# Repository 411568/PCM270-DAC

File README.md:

<h2>🧐 Features</h2>

USB DAC based on the PCM270xC iC. Powered by a USB type C connector. Output is compliant with the Line Out specification.
The included gerber files and BOM are made for JLCPCB. All of the components are taken from the LCSC library, meaning you can have the board assembled by JLC.
Important note: the board has not been tested yet.

<h2>🛡️ License:</h2>

This project is licensed under the MIT License.

<h2> 🙋‍♂️Authors </h2>

- Krzysztof Sikora

<h2>💖Like my work?</h2>

If you have any questions about the project feel free to contact us via email: krzysieksikora717@gmail.com

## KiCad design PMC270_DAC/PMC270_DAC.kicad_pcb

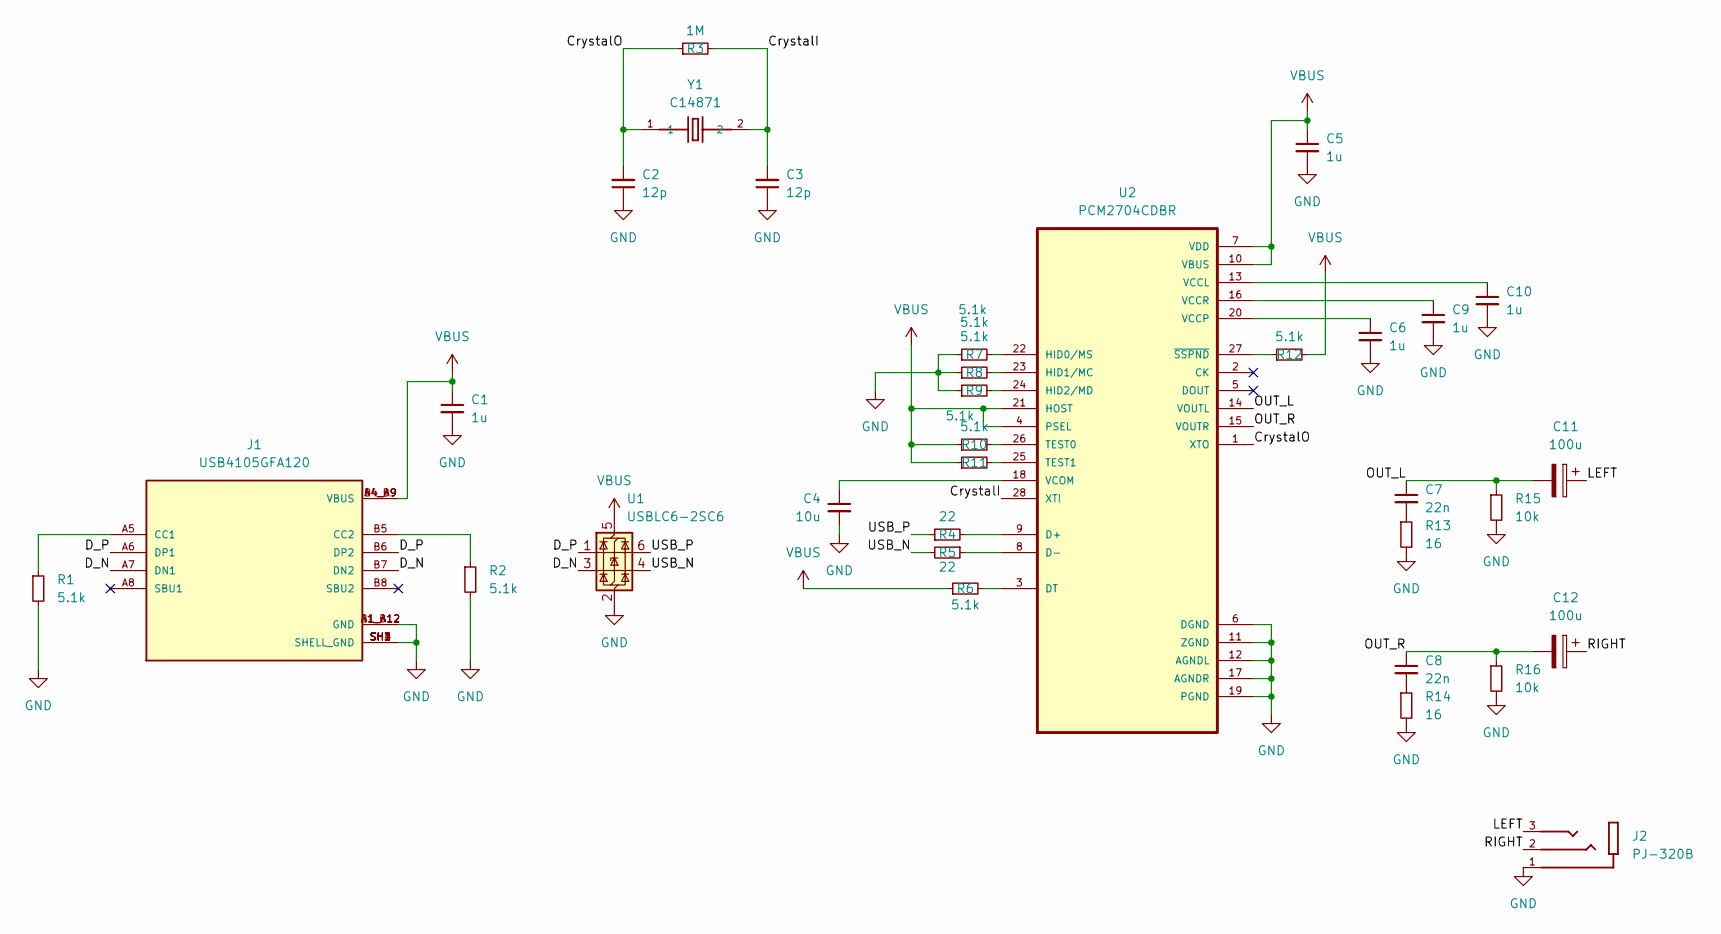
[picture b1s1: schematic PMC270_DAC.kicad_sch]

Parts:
C1, C5, C6, C9, C10: 1u; C_0805_2012Metric_Pad1.18x1.45mm_HandSolder
C2, C3: 12p; C_0603_1608Metric_Pad1.08x0.95mm_HandSolder
C4: 10u; C_0805_2012Metric_Pad1.18x1.45mm_HandSolder
C7, C8: 22n; C_0603_1608Metric_Pad1.08x0.95mm_HandSolder
C11, C12: 100u; C_Elec_6.3x7.7
J1: USB4105GFA120; GCT_USB4105GFA120; PARTREV B3
J2: PJ-320B; BOOMELE_PJ-320B
R1, R2, R6, R7, R8, R9, R10, R11, R12: 5.1k; R_0603_1608Metric_Pad0.98x0.95mm_HandSolder
R3: 1M; R_0603_1608Metric_Pad0.98x0.95mm_HandSolder
R4, R5: 22; R_0603_1608Metric_Pad0.98x0.95mm_HandSolder
R13, R14: 16; R_0603_1608Metric_Pad0.98x0.95mm_HandSolder
R15, R16: 10k; R_0603_1608Metric_Pad0.98x0.95mm_HandSolder
U1: USBLC6-2SC6; SOT-23-6
U2: PCM2704CDBR; SOP65P780X200-28N
Y1: C14871; XTAL1170X500X450

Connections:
/CrystalI: C3.2, R3.2, U2.28 (XTI), Y1.2
/CrystalO: C2.2, R3.1, U2.1 (XTO), Y1.1
/D_N: J1.A7 (DN1), J1.B7 (DN2), U1.3 (I/O2); also elsewhere on the board
/D_P: J1.A6 (DP1), J1.B6 (DP2), U1.1 (I/O1); also elsewhere on the board
/LEFT: C11.1, J2.3; also elsewhere on the board
/OUT_L: C7.1, C11.2, R15.1, U2.14 (VOUTL)
/OUT_R: C8.1, C12.2, R16.1, U2.15 (VOUTR)
/RIGHT: C12.1, J2.2; also elsewhere on the board
/USB_N: R5.2, U1.4 (I/O2)
/USB_P: R4.1, U1.6 (I/O1)
GND: C1.2, C2.1, C3.1, C4.2, C5.2, C6.2, C9.2, C10.2, J1.A1_B12 (GND), J1.B1_A12 (GND), J1.SH1 (SHELL_GND), J1.SH2 (SHELL_GND), J1.SH3 (SHELL_GND), J1.SH4 (SHELL_GND), J2.1, R1.2, R2.2, R7.1, R8.1, R9.1, R13.2, R14.2, R15.2, R16.2, U1.2 (GND), U2.6 (DGND), U2.11 (ZGND), U2.12 (AGNDL), U2.17 (AGNDR), U2.19 (PGND); also elsewhere on the board
unnamed: C7.2, R13.1
unnamed: C8.2, R14.1
unnamed 13: J1.A5 (CC1), R1.1; also elsewhere on the board
unnamed 14: J1.B5 (CC2), R2.1; also elsewhere on the board
unnamed: R4.2, U2.9 (D+)
unnamed: R5.1, U2.8 (D-)
unnamed: R6.2, U2.3 (DT)
unnamed: R7.2, U2.22 (HID0/MS)
unnamed: R8.2, U2.23 (HID1/MC)
unnamed: R9.2, U2.24 (HID2/MD)
unnamed: R10.2, U2.26 (TEST0)
unnamed: R11.2, U2.25 (TEST1)
unnamed: C10.1, U2.13 (VCCL)
unnamed: C6.1, U2.20 (VCCP)
unnamed: C9.1, U2.16 (VCCR)
unnamed: C4.1, U2.18 (VCOM)
unnamed: R12.1, U2.27 (~SSPND)
VBUS: C1.1, C5.1, J1.A4_B9 (VBUS), J1.B4_A9 (VBUS), R6.1, R10.1, R11.1, R12.2, U1.5 (VBUS), U2.4 (PSEL), U2.7 (VDD), U2.10 (VBUS), U2.21 (HOST); also elsewhere on the board

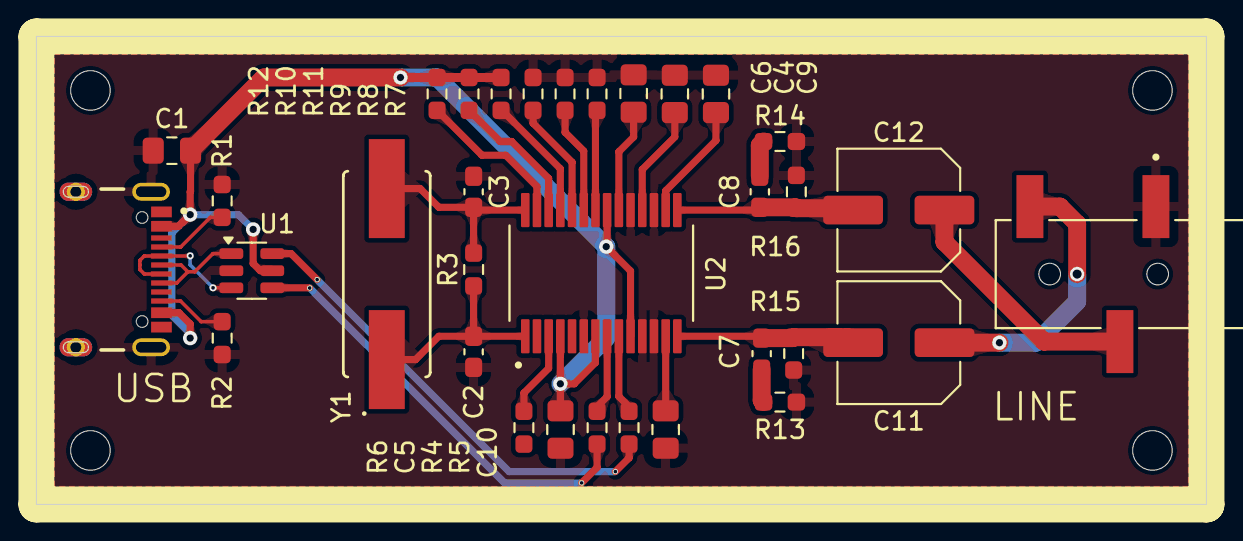
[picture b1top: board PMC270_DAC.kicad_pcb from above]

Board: 2 copper layers, 65.0 x 26.0 mm, 33 parts (0 on the bottom side), 29 nets.

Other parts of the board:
LINE: PJ-320B; BOOMELE_PJ-320B
USB: USB4105GFA120; GCT_USB4105GFA120

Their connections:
/D_N: USB.A7 (DN1), USB.B7 (DN2); also elsewhere on the board
/D_P: USB.A6 (DP1), USB.B6 (DP2); also elsewhere on the board
/LEFT: LINE.3; also elsewhere on the board
/RIGHT: LINE.2; also elsewhere on the board
GND: LINE.1, USB.A1_B12 (GND), USB.B1_A12 (GND), USB.SH1 (SHELL_GND), USB.SH2 (SHELL_GND), USB.SH3 (SHELL_GND), USB.SH4 (SHELL_GND); also elsewhere on the board
unnamed 13: USB.A5 (CC1); also elsewhere on the board
unnamed 14: USB.B5 (CC2); also elsewhere on the board
VBUS: USB.A4_B9 (VBUS), USB.B4_A9 (VBUS); also elsewhere on the board

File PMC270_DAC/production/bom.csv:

Designator,Footprint,Quantity,Value,LCSC Part #
"C1, C10, C5, C6, C9",0805,5,1u,
"C11, C12",C_Elec_6.3x7.7,2,100u,
"C2, C3",0603,2,12p,
C4,0805,1,10u,
"C7, C8",0603,2,22n,
LINE,BOOMELE_PJ-320B,1,PJ-320B,
"R1, R10, R11, R12, R2, R6, R7, R8, R9",0603,9,5.1k,
"R13, R14",0603,2,16,
"R15, R16",0603,2,10k,
R3,0603,1,1M,
"R4, R5",0603,2,22,
U1,SOT-23-6,1,USBLC6-2SC6,
U2,SOP65P780X200-28N,1,PCM2704CDBR,
USB,GCT_USB4105GFA120,1,USB4105GFA120,
Y1,XTAL1170X500X450,1,C14871,

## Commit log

2025-02-20 Added production files
2025-02-20 added readme
2025-02-20 added enclosure model
